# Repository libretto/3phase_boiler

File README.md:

# 3phase boiler controller project
Arduino based control unit circuit and firmware

# WARNING!!!  This code was created for my own test and study purposes and finally was implemented in DIY project for three phase 360V heater.
# DISCLAIMER! Any reproducing of the unit and usage it with high voltage devices is at your own risk!

History of project: 
I had cheap 12kW (360V) water heater in home climate system which had a problem with contactor frequently and I replaced it few times per season. 
To avoid this issue I decide include Solid State Relays with digital thermostat to heater circuit (serial connection to contactor based termostat for better safety).
This solution replaced mechanical switching with spark which destroy contactor to semiconductor switching and algorithm in thermostat reduced switches of heater to possible minimum.
I decide create my own thermostat circuit using Arduino nano as module to which i can connect LCD, Encoder, Sensors and SSR (or magnetic relay for other appliances). 

Required units:

Arduino Nano, 
Encoder unit KY-040 (with 3 10k resistors on board), 
LCD 1602 with I2C adaptor, 
SSR Fotek SSR-40DA 3 pcs, 
DS18B20 thermal sensor with holder module 

List of all semiconductor components is included in Eagle project.

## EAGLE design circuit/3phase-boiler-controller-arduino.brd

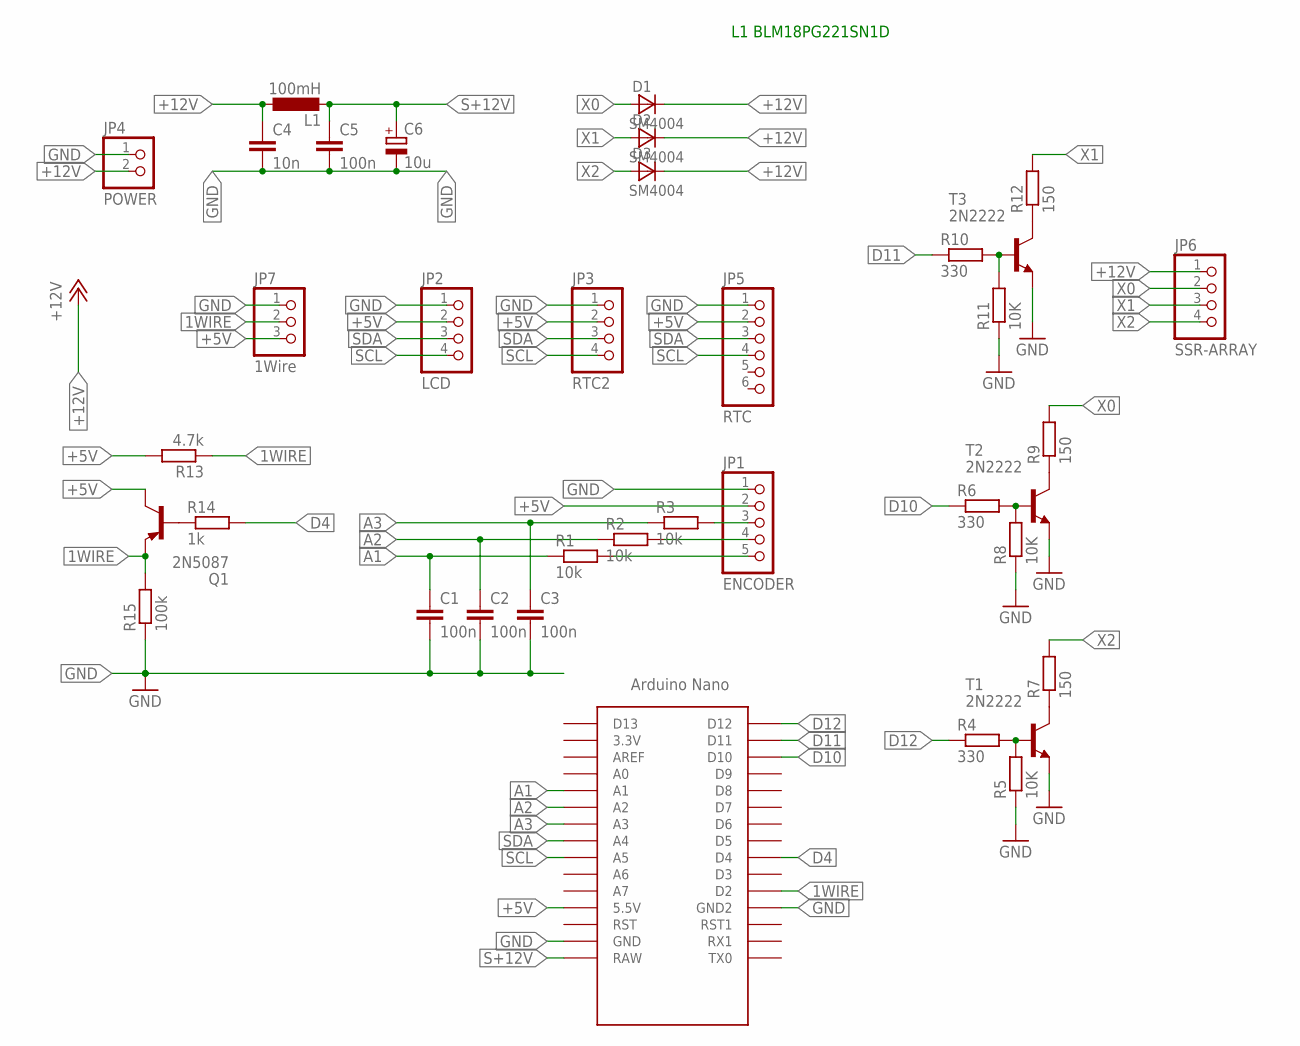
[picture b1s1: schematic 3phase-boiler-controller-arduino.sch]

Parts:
C1, C2, C3, C5: 100n; C0603
C4: 10n; C0603
C6: 10u; 153CLV-0807
D1, D2, D3: SM4004; MELF-MLL41
JP1: ENCODER; 1X05
JP2: LCD; 1X04
JP3: RTC2; 1X04
JP4: POWER; 1X02
JP5: RTC; 1X06/90
JP6: SSR-ARRAY; 1X04
JP7: 1Wire; 1X03
L1: 100mH; 0207/12
Q1: 2N5087; TO92
R1, R2, R3: 10k; R0805
R4, R6, R10: 330; R0805
R5, R8, R11: 10K; R0805
R7, R9, R12: 150; R0805
R13: 4.7k; R0805
R14: 1k; R0805
R15: 100k; R0805
T1, T2, T3: 2N2222; TO92-EBC-OVAL
U$1: NANO

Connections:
1WIRE: JP7.2, Q1.3 (E), R13.1, R15.2, U$1.D2
+5V: JP1.2, JP2.2, JP3.2, JP5.2, JP7.3, Q1.1 (C), R13.2, U$1.5V (5.5V)
+12V: C4.1, D1.C, D2.C, D3.C, JP4.2, JP6.1, L1.1
A1: C1.1, R1.1, U$1.A1
A2: C2.1, R2.1, U$1.A2
A3: C3.1, R3.1, U$1.A3
CLK: JP1.5, R1.2
D4: R14.2, U$1.D4
D10: R6.1, U$1.D10
D11: R10.1, U$1.D11
D12: R4.1, U$1.D12
DT: JP1.4, R2.2
GND: C1.2, C2.2, C3.2, C4.2, C5.2, C6.-, JP1.1, JP2.1, JP3.1, JP4.1, JP5.1, JP7.1, R5.1, R8.1, R11.1, R15.1, T1.E, T2.E, T3.E, U$1.GND, U$1.GND1 (GND2)
unnamed: R6.2, R8.2, T2.B
unnamed: R9.1, T2.C
unnamed: R10.2, R11.2, T3.B
unnamed: R12.1, T3.C
unnamed: R4.2, R5.2, T1.B
unnamed: R7.1, T1.C
unnamed: Q1.2 (B), R14.1
S+12V: C5.1, C6.+, L1.2, U$1.RAW
SCL: JP2.4, JP3.4, JP5.4, U$1.A5
SDA: JP2.3, JP3.3, JP5.3, U$1.A4
SW: JP1.3, R3.2
X0: D1.A, JP6.2, R9.2
X1: D2.A, JP6.3, R12.2
X2: D3.A, JP6.4, R7.2

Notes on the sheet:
L1 BLM18PG221SN1D

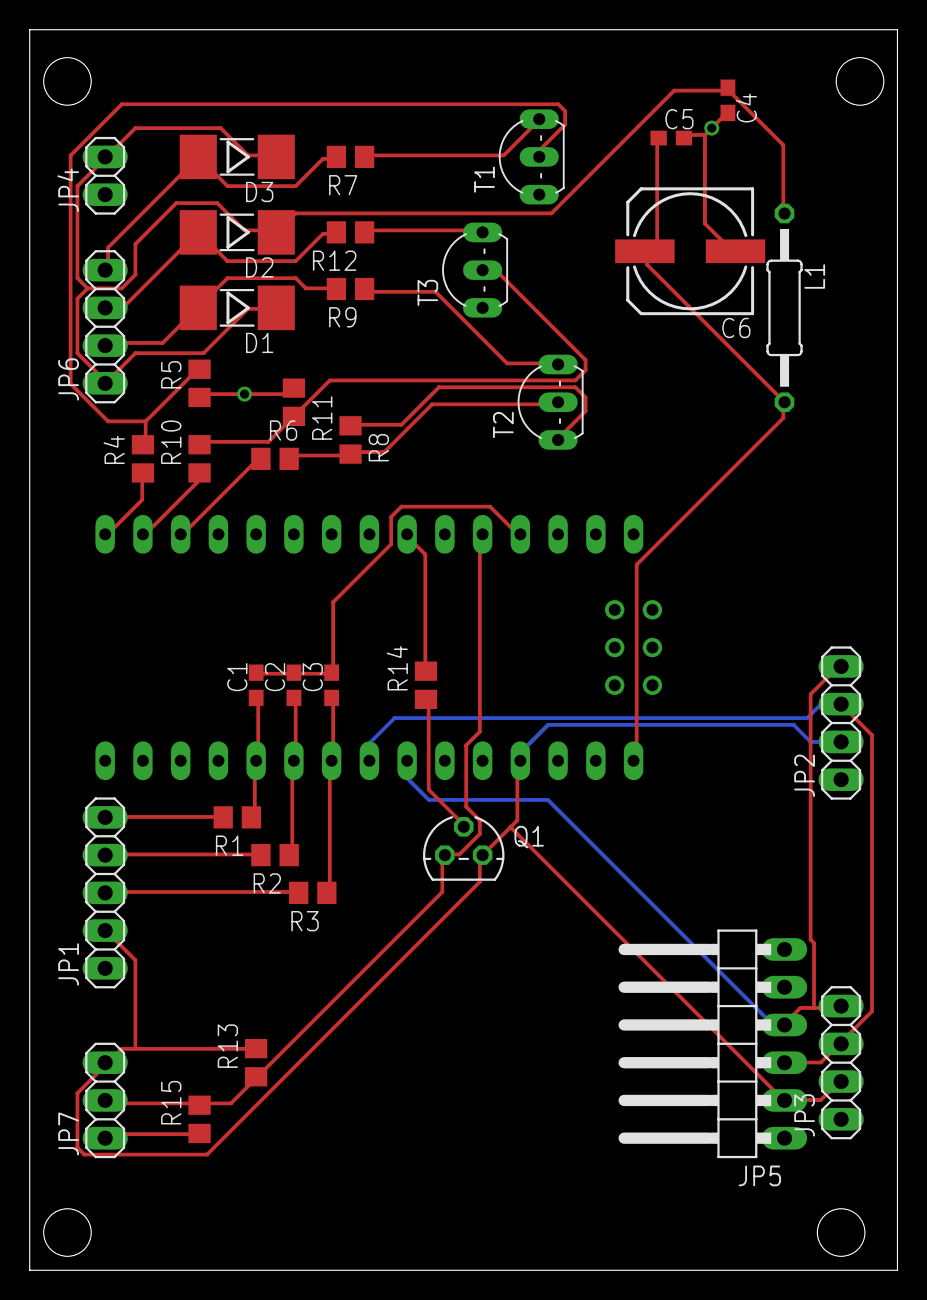
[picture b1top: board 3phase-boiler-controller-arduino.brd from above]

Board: 2 copper layers, 58.4 x 83.5 mm, 37 parts (0 on the bottom side), 27 nets.

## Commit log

2016-05-17 Init
2016-05-22 workaround with IRLib
2016-07-14 fixup
2020-01-14 beta release
2020-01-14 modify name
2020-01-15 change function names and update logic delays for smooth power change
2020-01-15 tune timing
2020-01-15 fixup timeouts
2020-01-16 debug speed 1-wire timing
2020-01-20 tune logic, add watchdog, improve encoder handler to minimize interrupt time
2020-01-20 fixup screen modes, add debug/log screen
